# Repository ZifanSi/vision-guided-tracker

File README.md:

<p align="center" width="100%">
   <br/>
   
</p>

<h1 align="center">
   RoCam: High Performance Vision-Guided Rocket Tracker  
</h1>

**Developer Names**: Zifan Si, Jianqing Liu, Mike Chen, Xiaotian Lou  
**Supervisor**: Shahin Sirouspour  

Date of project start: September 8th 2025  

**Project Overview**: The goal of this project is to design and implement a deployable camera tracking system capable of autonomously locking onto and following extremely fast-moving model rockets. The system integrates computer vision, motion control, and a web-based operator interface to deliver smooth, stable video (1080p @ 60fps) of critical rocket events such as staging and parachute deployment.  

This project builds a software stack that interfaces with low-cost hardware for small-scale launches (200m apogee) and is scalable to support the McMaster Rocketry Team’s high-powered rockets (3km+ apogee).  

---

### **Key Features**  

1. **Gimbal Motion Control**
   - Real-time two-axis gimbal control.
   - Closed-loop predictive control system for smooth and accurate motion.

2. **Computer Vision Pipeline**
   - Detects and tracks fast-moving objects in real time.
   - Maintains lock even with partial occlusion.
   - Digital zooming and stablization.

3. **Web Application**
   - Live video feed preview.
   - Operator controls for manual override and tracking adjustments.
   - Start/stop video recording, playback, and download.

4. **System Integration & Deployment**
   - Real-time tracking video output at 1080p/60fps.
   - Reliable and scalable for both small-scale and high-powered rocket launches.
   - Designed for ease of use, testing, and future expansion.

---

The folders and files for this project are as follows:  

- **docs** - Project documentation, design notes, diagrams
- **refs** - Reference materials (papers, hardware specs, related work)
- **src** - Source code for embedded system, CV pipeline, and web app
- **test** - Test cases, simulation data, and validation results

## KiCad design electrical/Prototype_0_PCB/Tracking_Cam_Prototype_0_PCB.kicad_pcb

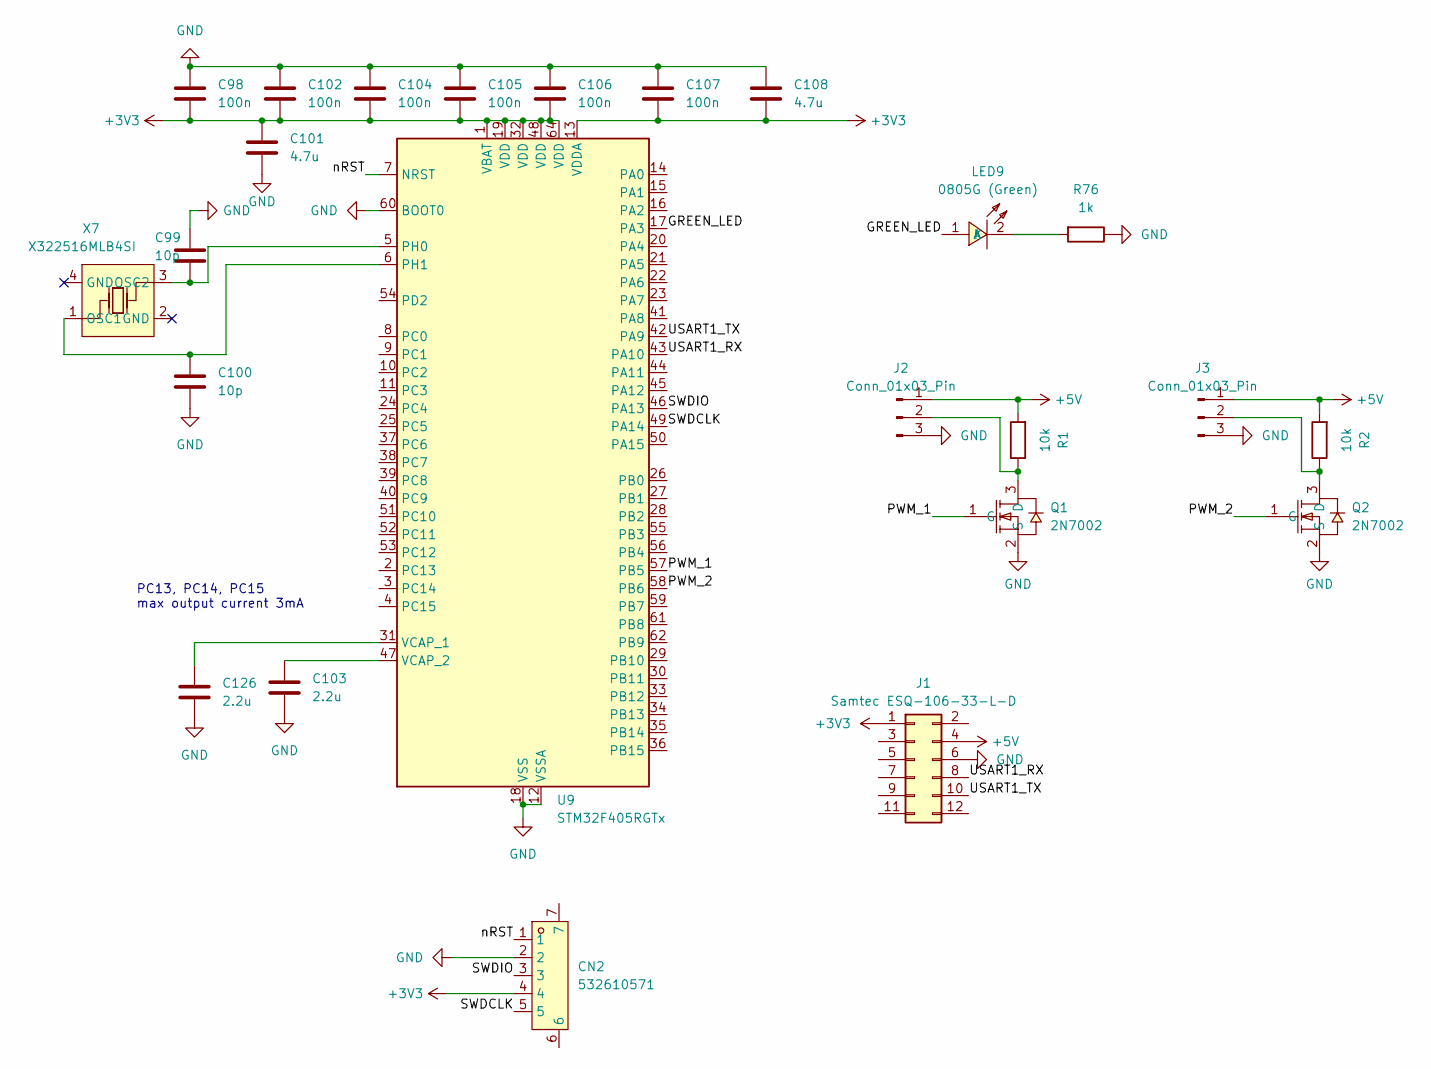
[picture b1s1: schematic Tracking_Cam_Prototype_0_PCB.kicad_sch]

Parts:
C98, C102, C104, C105, C106, C107: 100n; C_0402_1005Metric
C99, C100: 10p; C_0402_1005Metric
C101, C108: 4.7u; C_0402_1005Metric
C103, C126: 2.2u; C_0402_1005Metric
CN2: 532610571; CONN-SMD_5P-P1.25_532610571-2; LCSC Part C392176
J1: Samtec ESQ-106-33-L-D; PinSocket_2x06_P2.54mm_Vertical
J2, J3: Conn_01x03_Pin; PinHeader_1x03_P2.54mm_Vertical
LED9: 0805G (Green); LED0805-R-RD; LCSC Part C2297
Q1, Q2: 2N7002; SOT-23-3_L2.9-W1.3-P1.90-LS2.4-BR; LCSC Part C8545
R1, R2: 10k; R_0603_1608Metric
R76: 1k; R_0603_1608Metric
U9: STM32F405RGTx; LQFP-64_10x10mm_P0.5mm
X7: X322516MLB4SI; OSC-SMD_4P-L3.2-W2.5-BL; LCSC Part C13738

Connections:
+3V3: C98.2, C101.1, C102.2, C104.2, C105.2, C106.2, C107.2, C108.2, CN2.4, J1.1, U9.1 (VBAT), U9.13 (VDDA), U9.19 (VDD), U9.32 (VDD), U9.48 (VDD), U9.64 (VDD)
+5V: J1.4, J2.1, J3.1, R1.2, R2.2
/GREEN_LED: LED9.1 (A), U9.17 (PA3)
/PWM_1: Q1.1 (G), U9.57 (PB5)
/PWM_2: Q2.1 (G), U9.58 (PB6)
/SWDCLK: CN2.5, U9.49 (PA14)
/SWDIO: CN2.3, U9.46 (PA13)
/USART1_RX: J1.8, U9.43 (PA10)
/USART1_TX: J1.10, U9.42 (PA9)
/nRST: CN2.1, U9.7 (NRST)
GND: C98.1, C99.1, C100.2, C101.2, C102.1, C103.2, C104.1, C105.1, C106.1, C107.1, C108.1, C126.2, CN2.2, J1.6, J2.3, J3.3, Q1.2 (S), Q2.2 (S), R76.1, U9.12 (VSSA), U9.18 (VSS), U9.60 (BOOT0), U9.63 (VSS)
unnamed: J2.2, Q1.3 (D), R1.1
unnamed: J3.2, Q2.3 (D), R2.1
unnamed: LED9.2 (K), R76.2
unnamed: C99.2, U9.5 (PH0), X7.3 (OSC2)
unnamed: C100.1, U9.6 (PH1), X7.1 (OSC1)
unnamed: C126.1, U9.31 (VCAP_1)
unnamed: C103.1, U9.47 (VCAP_2)

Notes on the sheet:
PC13, PC14, PC15 max output current 3mA

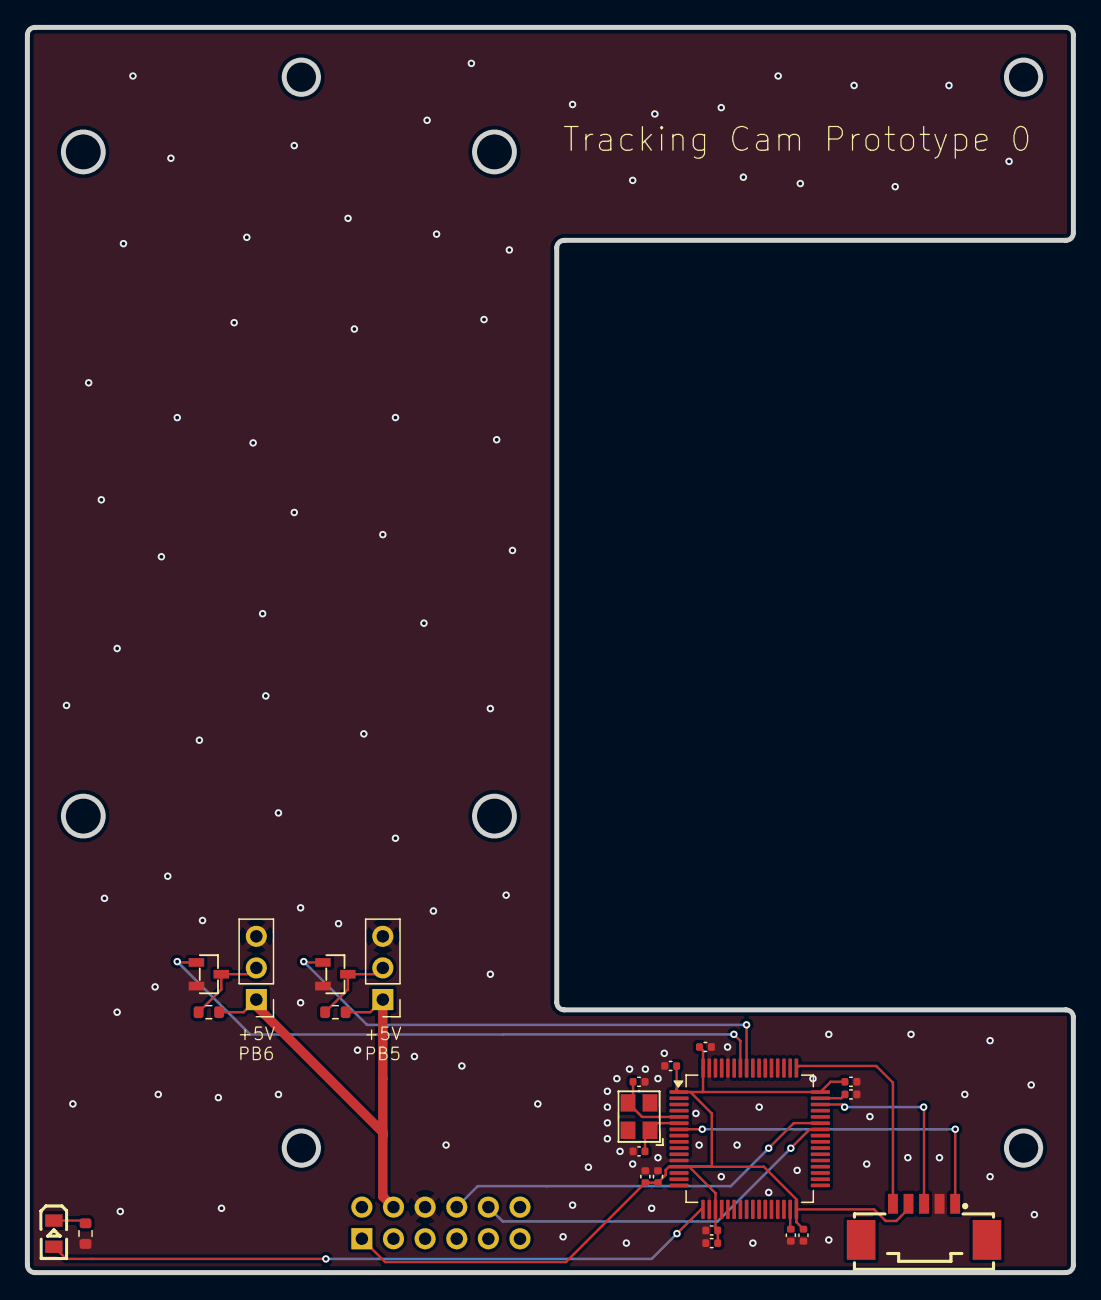
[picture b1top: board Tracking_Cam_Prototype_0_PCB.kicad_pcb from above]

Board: 2 copper layers, 84.0 x 100.0 mm, 24 parts (1 on the bottom side), 18 nets.

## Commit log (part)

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2025-09-23 Add/Update PDFs for changed LaTeX files: DevelopmentPlan.tex ProblemStatement.tex
2025-09-23 Add/Update PDF for changed LaTeX file: DevelopmentPlan.tex
2025-09-23 Add justifications for P4 to P11
2025-09-23 Add/Update PDF for changed LaTeX file: ProblemStatement.tex
2025-09-23 development plan reflection
2025-09-23 problem statement
2025-09-23 Fix Format issue
2025-09-23 Update Development Plan Reflection for Frank
2025-09-23 Update dev log and fix format issue
2025-09-23 Update readme for development plan
2025-09-23 Update readme for problem statement and goals
2025-09-23 Update Appendix with more details
2025-09-23 reproducible pdf
2025-09-23 check tex
2025-09-23 format all tex
2025-09-23 test ci
2025-09-23 format, fix ci
2025-09-23 allow manual trigger build tex
2025-09-23 dirty tex
2025-09-23 try to fix ci
2025-09-23 Format LaTeX files
2025-09-23 Add/Update PDFs
2025-09-23 dirty srs
2025-09-23 revert git-auto-commit-action to v4
2025-09-23 rename job
2025-09-23 update latex auto build settings
2025-09-27 Initialize React environment in src/react-app
2025-09-27 use Volere template
2025-09-27 add readme and makefile
2025-09-28 Update react CI
2025-09-28 Test small change to trigger CI
2025-09-28 Add minimal App.test to satisfy CI
2025-09-28 arabic page numbering
2025-09-28 Add a sample test case
2025-09-28 attempt to plug SAM and DINO to label data (buggy)
2025-09-29 bug fixed. but issue with the pipline operation logistics and code readability
2025-10-01 make problem statements more abstract
2025-10-02 stake holders and constraints
2025-10-02 Update basic TA meeting Note for Oct 10
2025-10-02 Add functional requirements
2025-10-02 Decompose FReq into SYS + WEB
2025-10-02 Appearance Requirements
2025-10-02 Style Requirements
2025-10-02 ease fo use Requirements
2025-10-02 Personalization and Internationalization Requirements
2025-10-02 Learning Requirements
2025-10-02 Understandability and Politeness Requirements
2025-10-02 Accessibility Requirements
2025-10-02 Speed and Latency Requirements
2025-10-02 scope of the work
2025-10-02 Safety-Critical Requirements
2025-10-02 Precision or Accuracy Requirements
2025-10-02 Robustness or Fault-Tolerance Requirements
2025-10-02 Capacity Requirements
2025-10-02 Scalability or Extensibility Requirements
2025-10-02 Longevity Requirements
2025-10-02 Expected Physical Environment
2025-10-02 Wider Environment Requirements
2025-10-02 Requirements for Interfacing with Adjacent Systems
2025-10-02 Productization Requirements
2025-10-02 Release Requirements
2025-10-02 Maintenance Requirements&Supportability Requirements&Adaptability Requirements
2025-10-02 Access Requirements&Integrity Requirements&Privacy Requirements&Audit Requirements&Immunity Requirements
2025-10-02 scope of the product
2025-10-02 Cultural Requirements
2025-10-02 Legal Requirements & Standards Compliance Requirements
2025-10-02 added pure math approach
2025-10-05 Fix "You need at least one paragraph before starting the subsections"
2025-10-05 Fix typo
2025-10-05 Fix "I love the way you described the problem and the citations, but there is a lack of connection between this and your work. You should explain you what you want to address"
2025-10-05 Fix "of what?"
2025-10-05 Fix "Does everyone know what gimbal is? It would be better to mention it earlier"
2025-10-05 Fix "I understand what you mean because we discussed in person. I don't think if a random person reads it, they can easily understand what you mean. It is almost ambiguous"
2025-10-05 fix "What is the difference between this and the previous one?"
2025-10-05 Fix "as input"
2025-10-05 Fix "You can have it more general and in the description mention his name."
2025-10-05 Fix "Goal It is not clear enough. As we discussed in the meeting you should explain all the goals you have"
2025-10-05 Fix "At least a paragraph is needed here extra"
2025-10-05 Fix which document? hyperlink
2025-10-05 Fix Entire Appendix
2025-10-05 fix blue text
2025-10-05 add dev logs
2025-10-05 Fix "I believe you can remove this and have your comments as a single paragraph without your names"
2025-10-05 Fix "mention if these roles are fixed or not. If they are fixed, who is responsible for each?"
2025-10-05 fix "At least a paragraph needed" for Workflowplan
2025-10-05 Fix "Fix the format as I said in the other one"
2025-10-05 Fix "istead say table 2 and use \ref to reference it"
2025-10-05 Fix to PoC
2025-10-05 Fix "such as?"
2025-10-05 fix "hyper link"
2025-10-05 Fix microcontroller such as
2025-10-05 Fix Appendix — Reflection based on "I believe you can remove this and have your comments as a single paragraph without your names"
2025-10-05 Fix "such as" by adding more concrete exampless
2025-10-05 Update fix logs
2025-10-06 latex not working for long table
2025-10-06 reset git changes before formatting
2025-10-08 update stakeholders and requirements
2025-10-08 assumptions
2025-10-09 The Scope of the Work and Product WIP
2025-10-09 business use cases
2025-10-10 Update SRS rubric
2025-10-10 Update SRS Rubric copy from A2L
2025-10-10 Update Hazard Analysis Rubric
2025-10-10 refined PUC and BUC table
2025-10-10 update requirement detail
2025-10-10 product use case
2025-10-10 glossary
2025-10-10 should be done, should pass CI
2025-10-10 data dictionary
2025-10-10 update functional requirements
2025-10-10 Update requirements
2025-10-11 draft section 18-24
2025-10-11 NFR changes
2025-10-11 format requirements
2025-10-11 assign source PUC and priority to every requirement
2025-10-11 update revision history
2025-10-11 update requirement
2025-10-11 reflection WIP
2025-10-11 Update 16 to 24
2025-10-11 reflection
2025-10-13 label_pipeline_complete + Jetson intial deployment
2025-10-13 temperal commit
2025-10-14 add pcb firmware
2025-10-16 control servo
2025-10-16 echo task
2025-10-17 add api
2025-10-17 add example call
2025-10-17 add requirement.txt for api
2025-10-17 update api
2025-10-17 Fix button text for right direction in example_call.html
2025-10-18 Update basic ui from Top left cam and Bottom right gimbal pad
2025-10-18 Fix button light
2025-10-19 Fix backend and decompose frontend
2025-10-19 add steam
2025-10-19 Make code more SOLID
2025-10-19 Update TOP RIGHT section and fix api
2025-10-19 Update dev read me
2025-10-19 Refactor react-ci.yml for improved clarity
    Updated CI workflow for React app to simplify steps and paths.
2025-10-19 CI test
2025-10-19 Add mock CI
2025-10-19 Refactor CI workflow for better dependency handling
    Updated CI workflow to improve dependency installation and testing steps.
2025-10-19 Fix CI root to test/ci-ok.js
2025-10-19 Fix React test roots
2025-10-19 Update mock CI
2025-10-19 Section 1-3, generally done
2025-10-23 small changes
2025-10-26 fixed section 3 and previous comments
2025-10-26 update log
2025-10-27 reflection commit
2025-10-28 add system tests
2025-10-28 add reflection
2025-10-28 servo and led
2025-10-28 update dependencies
2025-10-28 firmware ci
2025-10-28 fix ci
2025-10-28 update ci
2025-10-28 save
2025-10-28 update and save
2025-10-30 calibrate
2025-10-31 tensorRt fp16
2025-10-31 Add Sensitivity and Zoom
2025-10-31 update .gitignore so pyc is not committed
2025-10-31 Remoeve some texts from sensitive and zoom
2025-10-31 Update gitignore
2025-10-31 save backend
2025-10-31 Create reset camera
2025-11-02 Module guide
2025-11-03 Update prototype as sub logo to readme
2025-11-03 Fix assets name
2025-11-03 modify team contrib
2025-11-03 update attendance
2025-11-03 update issue tracker
2025-11-03 temp commit
2025-11-03 update commit
2025-11-04 update name
2025-11-04 Tracibility matrix complete
2025-11-04 update demo plan
2025-11-04 update CICD
2025-11-04 update Team Charter Trigger Items
2025-11-04 update explanation
2025-11-04 remove submodule to clear up
2025-11-04 Elaborate on React CI
2025-11-04 Add img folder to put all non logo stuff
2025-11-04 Add Demo 3d model
2025-11-04 Update disarm and arm to manual and auto and set colors
2025-11-04 section 9 use hierarchy diagram done
2025-11-05 save weight(temp)
2025-11-05 Create FLOP TEST
2025-11-06 training in runnin
2025-11-06 update MIS
2025-11-07 Update demo vids
2025-11-07 Add demo vids
2025-11-09 saving some progress
2025-11-09 fix cmd
2025-11-09 update for connection
2025-11-09 update step
2025-11-09 Add controller page and Videro page
2025-11-09 add threaded
2025-11-09 update ip
2025-11-09 add Gimbal.py author:@pega
2025-11-10 update api back
2025-11-10 update api update
2025-11-10 update MG and MIS
2025-11-11 save rotation
2025-11-11 commit for cv part
2025-11-11 add gimbal part
2025-11-11 add poc benchmark
2025-11-11 Fix docs based on peer review (#71)
2025-11-11 Fix Peer Review - Supervisor listed as direct stakeholder (#67)
2025-11-13 Add Navbar and its css layout
2025-11-13 Update to a general page
2025-11-13 wrapped by the .container layout.
2025-11-13 Add control page
2025-11-13 Add video page
2025-11-13 Update css
2025-11-13 set to fix
2025-11-13 Add mock uis
2025-11-13 Update grids
2025-11-13 update to dji ratio
2025-11-13 Small fix
2025-11-13 Update gimble status
2025-11-13 Update video pane
2025-11-13 Add Env setting
2025-11-13 rename RoCam
2025-11-13 minor wording changes & dependency fix
2025-11-13 upload the best weight yet
2025-11-13 update parameter
2025-11-13 move cv folder to backend
2025-11-14 save update
2025-11-14 save update2
2025-11-14 save finished
2025-11-14 add light
2025-11-14 add light finished
2025-11-14 update path
2025-11-14 Add debugging
2025-11-14 Add basic mode and its hock uder TR
2025-11-14 Add lens, iso and shutter
2025-11-14 save pid
2025-11-15 refactoring poc
2025-11-15 done, most of the issues
2025-11-15 backend api server
2025-11-15 remove unused files
2025-11-15 bug fixes
2025-11-16 rewrote frontend
2025-11-16 update navbar
2025-11-16 setup react ci
2025-11-16 commit yarn.lock
2025-11-16 serve static files
2025-11-16 fix peer review comments for MG and MIS
2025-11-17 address SRS peer review issues
2025-11-17 Close peer review #110: add STM32/Jetson solution constraints and note in 19.2
2025-11-18 deepstream yolo
2025-11-18 deepstream
2025-11-19 deepstream opengl composing
2025-11-19 preview wip
2025-11-19 tune recording quality
2025-11-19 refactor previewing
2025-11-20 cv in saparate process
2025-11-20 implement tracking, remove old deepstream code
2025-11-20 tried to deploy SAM3, but don't have access to weight yet, hopefully soon
2025-11-20 digital stablization
2025-11-20 fix lint
2025-11-20 add model files
2025-11-20 update weights
2025-11-20 Sync model.pt
2025-11-21 update convert script
2025-11-21 deployment script
2025-11-21 fix gimbal communication errors, add auto scaling
2025-11-22 switch dependency back to git version
2025-11-22 setup initial folder
